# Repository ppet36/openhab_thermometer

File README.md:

# OpenHAB thermo & humidity meter

This repository contains Cadsoft's Eagle schematic and PCBs as well as Arduino firmware for simple temperature and humidity meter based on ESP8266-01 and AM2302 sensor. Meter is divided into two parts; indoor part with ESP and outdoor part with sensor.

For powering unit is used cheap DC/DC converter with LM2596 from eBay (previously set to 3.3V!!!); in my case is power supply shared with motorized venetian blinds in kitchen; they have 24VDC. Switching DC/DC converter seems to be overkill, but when voltage drop is too large (in my case around 21V) linear ones generates much heat and thus this converter is economical variant.

### Indoor part schematic

### Outdoor part schematic

Firmware can be programmed from Arduino IDE. For compilation is needed AM library from Adafruit which can be downloaded from https://learn.adafruit.com/dht/downloads. WIFI access point and network parameters can be set in source code. After device startup is on his IP address available HTTP server which provides measured temperature and humidity values as REST services. Via HTTP server is also available simple configuration page.

PCB boards is designed as single-sided. Indoor part of thermometer is placed in rectangular electrical ducting. For outdoor part i created simple model, which is available in openscad directory.

### OpenHAB
OpenHAB definition is also very simple. You need to edit your items and sitemap files. In items file is needed to add definition of services (replace IP address with IP address of your device):
```
Number outdoorTemperature "Outdoor temperature [%.1f °C]" <temperature> { http="<[http://192.168.128.205/temperature:15000:JS(doublevalue.js)]" }
Number outdoorHumidity "Outdoor humidity [%.1f %%]" <water> { http="<[http://192.168.128.205/humidity:15000:JS(doublevalue.js)]" }
```
In short this defines two numbers, which is readed from given URLs every 15 seconds and readed values is converted using script doublevalue.js. Finally can be measured values added to your sitemap file:
```    
Text item=outdoorTemperature
Text item=outdoorHumidity
```
After successfull configuration are available measured values on OpenHAB page:

## Some project images

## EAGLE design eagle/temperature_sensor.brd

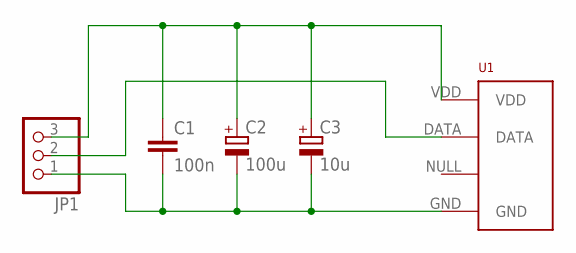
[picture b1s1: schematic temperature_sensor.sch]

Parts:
C1: 100n; C050-024X044
C2: 100u; E2-5
C3: 10u; E1,8-4
JP1: PINHD-1X3; 1X03
U1: RHT03_DHT-22_AM2302RA; RHT03_DHT-22/RA

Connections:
unnamed: C1.2, C2.-, C3.-, JP1.1, U1.GND
unnamed: C1.1, C2.+, C3.+, JP1.3, U1.VDD
unnamed: JP1.2, U1.DATA

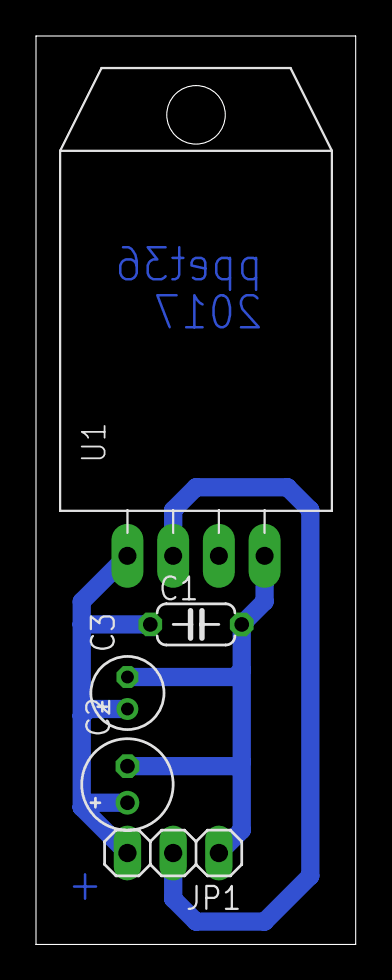
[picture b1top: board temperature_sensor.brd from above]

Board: 2 copper layers, 17.8 x 50.5 mm, 5 parts (0 on the bottom side), 3 nets.

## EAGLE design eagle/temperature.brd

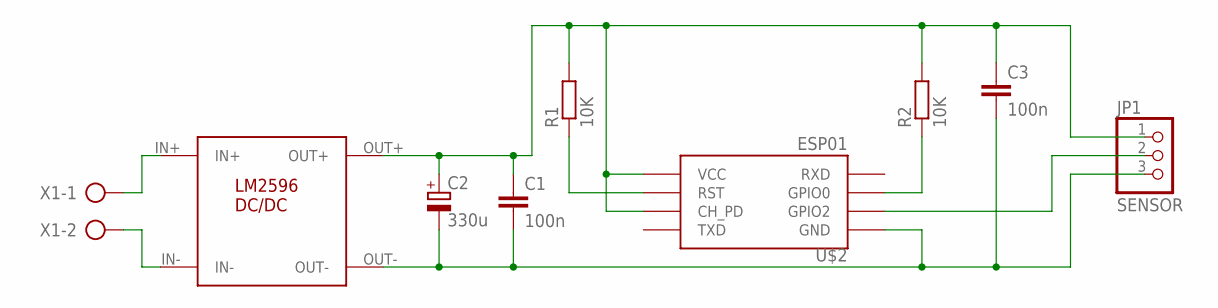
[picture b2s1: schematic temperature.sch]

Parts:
C1, C3: 100n; C050-024X044
C2: 330u; E2,5-6E
JP1: SENSOR; 1X03
R1, R2: 10K; 0204/7
U$1: LM2596DCDC
U$2: ESP01
X1: AK300/2

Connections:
GND: C1.2, C2.-, C3.2, JP1.3, U$1.OUT-, U$2.GND
unnamed: R2.1, U$2.GPIO0
unnamed: R1.1, U$2.RST
unnamed: U$1.IN+, X1.1
unnamed: JP1.2, U$2.GPIO2
unnamed: U$1.IN-, X1.2
VCC: C1.1, C2.+, C3.1, JP1.1, R1.2, R2.2, U$1.OUT+, U$2.CH_PD, U$2.VCC

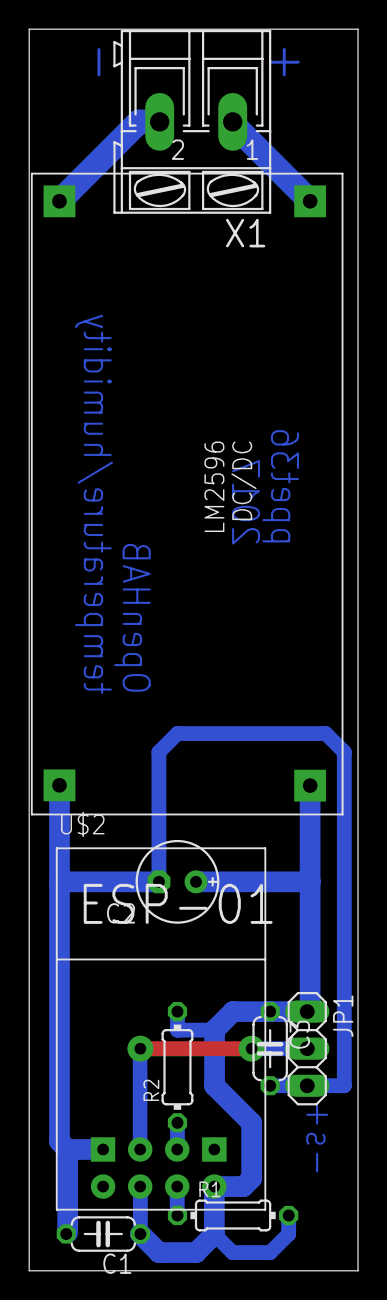
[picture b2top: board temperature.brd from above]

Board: 2 copper layers, 22.5 x 85.1 mm, 9 parts (0 on the bottom side), 7 nets.

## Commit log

2017-01-29 Added doublevalue.js
2017-01-30 Added posibility to periodically check WiFi connection
2017-01-31 Some improvements
2017-01-31 Small improvements
